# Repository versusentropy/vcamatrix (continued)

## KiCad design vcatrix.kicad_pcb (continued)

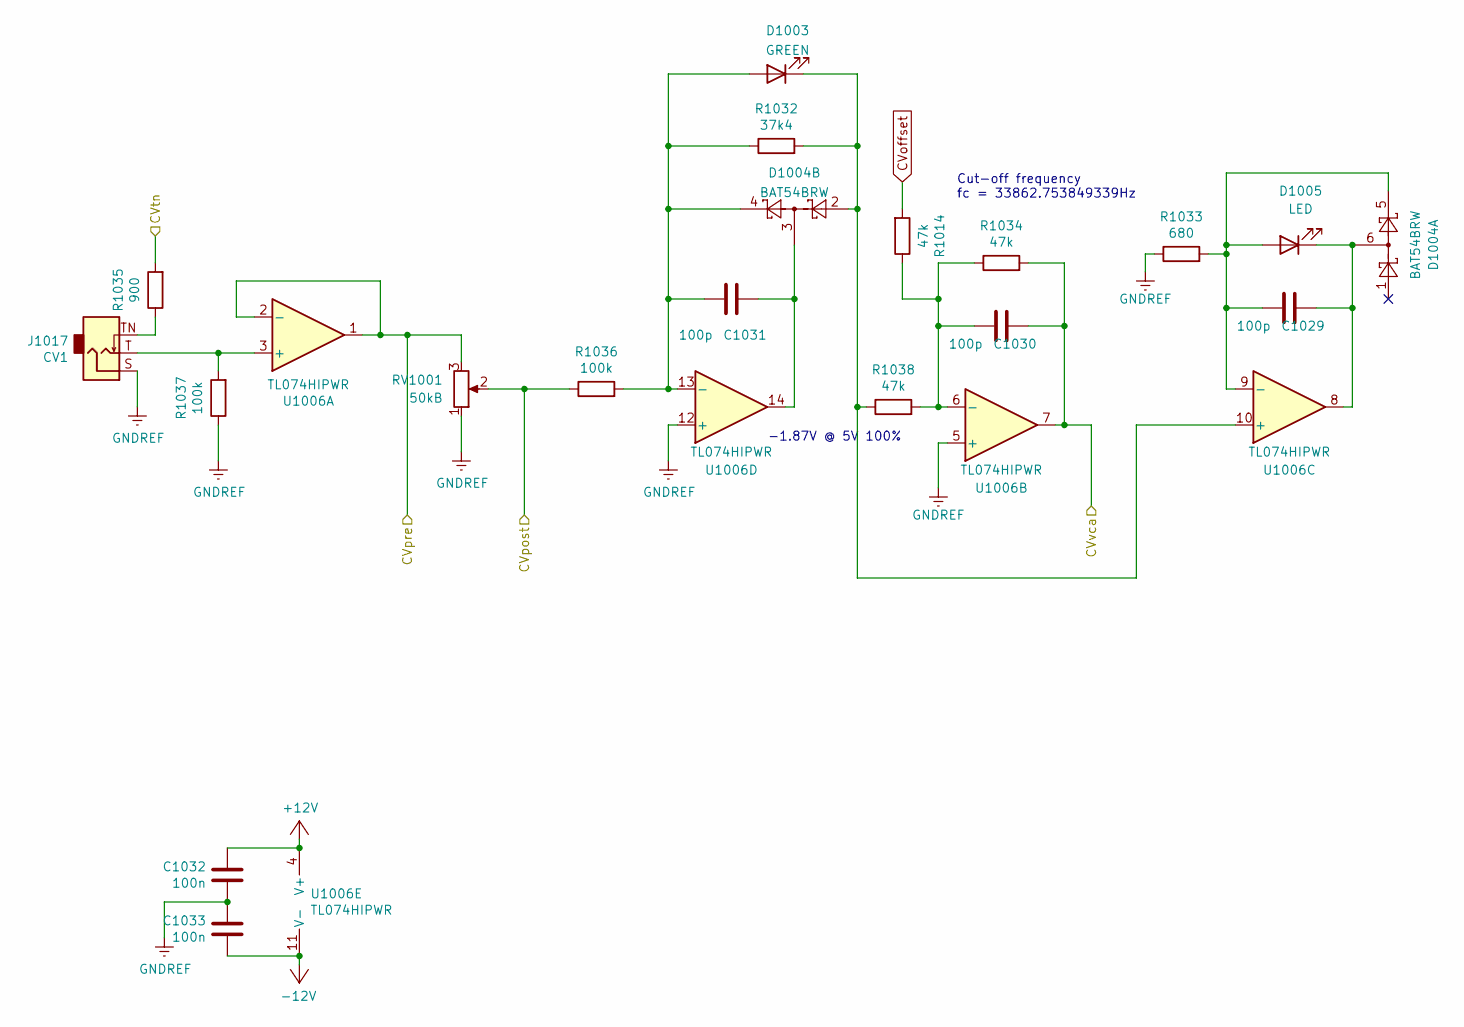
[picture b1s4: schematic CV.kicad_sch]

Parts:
C1029, C1030, C1031: 100p; C_0402_1005Metric; LCSC C1546
C1032, C1033: 100n; C_0402_1005Metric; LCSC C307331
D1003: GREEN; LED_0805_2012Metric; LCSC C98221
D1004: BAT54BRW; SOT-363_SC-70-6; LCSC C5240643
D1005: LED; LED_D3.0mm
J1017: CV1; Jack_3.5mm_QingPu_WQP-PJ398SM_Vertical_CircularHolesSMALL
R1014, R1034, R1038: 47k; R_0402_1005Metric; LCSC C358418
R1032: 37k4; R_0402_1005Metric; LCSC C103005
R1033: 680; R_0603_1608Metric; LCSC C23228
R1035: 900; R_0603_1608Metric; LCSC C3013565
R1036, R1037: 100k; R_0402_1005Metric; LCSC C317929
RV1001: 50kB; Potentiometer_Alpha_RD901F-40-00D_Single_Vertical
U1006: TL074HIPWR; TSSOP-14_4.4x5mm_P0.65mm; LCSC C4370424

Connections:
+12V: C1032.2, U1006.4 (V+); also elsewhere on the board
-12V: C1033.1, U1006.11 (V-); also elsewhere on the board
/5Vref: R1035.2; also elsewhere on the board
/VCA row1/CV-A/CVvca: C1030.1, R1034.2, U1006.7; also elsewhere on the board
/VCA row1/CVpostA: R1036.1, RV1001.2; also elsewhere on the board
/VCA row1/CVpreA: RV1001.3, U1006.1, U1006.2 (-); also elsewhere on the board
CVoffset: R1014.2; also elsewhere on the board
GNDREF: C1032.1, C1033.2, J1017.S, R1033.1, R1037.1, RV1001.1, U1006.5 (+), U1006.12 (+); also elsewhere on the board
unnamed: C1031.1, D1004.3, U1006.14
unnamed: C1031.2, D1003.2 (A), D1004.4, R1032.1, R1036.2, U1006.13 (-)
unnamed: D1003.1 (K), D1004.2, R1032.2, R1038.1, U1006.10 (+)
unnamed: C1029.2, D1004.5, D1005.2 (A), R1033.2, U1006.9 (-)
unnamed: C1029.1, D1004.6, D1005.1 (K), U1006.8
unnamed: J1017.TN, R1035.1
unnamed: J1017.T, R1037.2, U1006.3 (+)
unnamed: C1030.2, R1014.1, R1034.1, R1038.2, U1006.6 (-)

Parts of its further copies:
C1101, C1102, C1103, C1201, C1202, C1203, C1301, C1302, C1303, C2001, C2002, C2003, C2101, C2102, C2103, C2201, C2202, C2203, C2301, C2302, C2303, C3001, C3002, C3003, C3101, C3102, C3103, C3201, C3202, C3203, C3301, C3302, C3303, C4001, C4002, C4003, C4101, C4102, C4103, C4201, C4202, C4203, C4301, C4302, C4303: 100p; C_0402_1005Metric; LCSC C1546
C1104, C1105, C1204, C1205, C1304, C1305, C2004, C2005, C2104, C2105, C2204, C2205, C2304, C2305, C3004, C3005, C3104, C3105, C3204, C3205, C3304, C3305, C4004, C4005, C4104, C4105, C4204, C4205, C4304, C4305: 100n; C_0402_1005Metric; LCSC C307331
D1101, D1201, D1301, D2001, D2101, D2201, D2301, D3001, D3101, D3201, D3301, D4001, D4101, D4201, D4301: GREEN; LED_0805_2012Metric; LCSC C98221
D1102, D1202, D1302, D2002, D2102, D2202, D2302, D3002, D3102, D3202, D3302, D4002, D4102, D4202, D4302: BAT54BRW; SOT-363_SC-70-6; LCSC C5240643
D1103, D1203, D1303, D2003, D2103, D2203, D2303, D3003, D3103, D3203, D3303, D4003, D4103, D4203, D4303: LED; LED_D3.0mm
J1101, J1201, J1301, J2001, J2101, J2201, J2301, J3001, J3101, J3201, J3301, J4001, J4101, J4201, J4301: CV1; Jack_3.5mm_QingPu_WQP-PJ398SM_Vertical_CircularHolesSMALL
R1015, R1016, R1017, R1018, R1023, R1024, R1025, R1026, R1027, R1028, R1029, R1030, R1031, R1053, R1054, R1103, R1107, R1203, R1207, R1303, R1307, R2003, R2007, R2103, R2107, R2203, R2207, R2303, R2307, R3003, R3007, R3103, R3107, R3203, R3207, R3303, R3307, R4003, R4007, R4103, R4107, R4203, R4207, R4303, R4307: 47k; R_0402_1005Metric; LCSC C358418
R1101, R1201, R1301, R2001, R2101, R2201, R2301, R3001, R3101, R3201, R3301, R4001, R4101, R4201, R4301: 37k4; R_0402_1005Metric; LCSC C103005
R1102, R1202, R1302, R2002, R2102, R2202, R2302, R3002, R3102, R3202, R3302, R4002, R4102, R4202, R4302: 680; R_0603_1608Metric; LCSC C23228
R1104, R1204, R1304, R2004, R2104, R2204, R2304, R3004, R3104, R3204, R3304, R4004, R4104, R4204, R4304: 900; R_0603_1608Metric; LCSC C3013565
R1105, R1106, R1205, R1206, R1305, R1306, R2005, R2006, R2105, R2106, R2205, R2206, R2305, R2306, R3005, R3006, R3105, R3106, R3205, R3206, R3305, R3306, R4005, R4006, R4105, R4106, R4205, R4206, R4305, R4306: 100k; R_0402_1005Metric; LCSC C317929
RV1101, RV1201, RV1301, RV2001, RV2101, RV2201, RV2301, RV3001, RV3101, RV3201, RV3301, RV4001, RV4101, RV4201, RV4301: 50kB; Potentiometer_Alpha_RD901F-40-00D_Single_Vertical
U1101, U1201, U1301, U2001, U2101, U2201, U2301, U3001, U3101, U3201, U3301, U4001, U4101, U4201, U4301: TL074HIPWR; TSSOP-14_4.4x5mm_P0.65mm; LCSC C4370424

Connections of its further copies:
+12V: C1104.2, C1204.2, C1304.2, C2004.2, C2104.2, C2204.2, C2304.2, C3004.2, C3104.2, C3204.2, C3304.2, C4004.2, C4104.2, C4204.2, C4304.2, U1101.4 (V+), U1201.4 (V+), U1301.4 (V+), U2001.4 (V+), U2101.4 (V+), U2201.4 (V+), U2301.4 (V+), U3001.4 (V+), U3101.4 (V+), U3201.4 (V+), U3301.4 (V+), U4001.4 (V+), U4101.4 (V+), U4201.4 (V+), U4301.4 (V+); also elsewhere on the board
-12V: C1105.1, C1205.1, C1305.1, C2005.1, C2105.1, C2205.1, C2305.1, C3005.1, C3105.1, C3205.1, C3305.1, C4005.1, C4105.1, C4205.1, C4305.1, U1101.11 (V-), U1201.11 (V-), U1301.11 (V-), U2001.11 (V-), U2101.11 (V-), U2201.11 (V-), U2301.11 (V-), U3001.11 (V-), U3101.11 (V-), U3201.11 (V-), U3301.11 (V-), U4001.11 (V-), U4101.11 (V-), U4201.11 (V-), U4301.11 (V-); also elsewhere on the board
/5Vref: R1104.2, R1204.2, R1304.2; also elsewhere on the board
/VCA row1/CV-B/CVvca: C1102.1, R1103.2, U1101.7; also elsewhere on the board
/VCA row1/CV-C/CVvca: C1202.1, R1203.2, U1201.7; also elsewhere on the board
/VCA row1/CV-D/CVvca: C1302.1, R1303.2, U1301.7; also elsewhere on the board
/VCA row1/CVpostB: R1105.1, RV1101.2; also elsewhere on the board
/VCA row1/CVpostC: R1205.1, RV1201.2; also elsewhere on the board
/VCA row1/CVpostD: R1305.1, RV1301.2; also elsewhere on the board
/VCA row1/CVpreB: RV1101.3, U1101.1, U1101.2 (-); also elsewhere on the board
/VCA row1/CVpreC: RV1201.3, U1201.1, U1201.2 (-); also elsewhere on the board
/VCA row1/CVpreD: RV1301.3, U1301.1, U1301.2 (-); also elsewhere on the board
/VCA row2/CV-A/CVvca: C2002.1, R2003.2, U2001.7; also elsewhere on the board
/VCA row2/CV-B/CVvca: C2102.1, R2103.2, U2101.7; also elsewhere on the board
/VCA row2/CV-C/CVvca: C2202.1, R2203.2, U2201.7; also elsewhere on the board
/VCA row2/CV-D/CVvca: C2302.1, R2303.2, U2301.7; also elsewhere on the board
/VCA row2/CVpostA: R2005.1, RV2001.2
/VCA row2/CVpostB: R2105.1, RV2101.2
/VCA row2/CVpostC: R2205.1, RV2201.2
/VCA row2/CVpostD: R2305.1, RV2301.2
/VCA row2/CVpreA: R3004.2, RV2001.3, U2001.1, U2001.2 (-)
/VCA row2/CVpreB: R3104.2, RV2101.3, U2101.1, U2101.2 (-)
/VCA row2/CVpreC: R3204.2, RV2201.3, U2201.1, U2201.2 (-)
/VCA row2/CVpreD: R3304.2, RV2301.3, U2301.1, U2301.2 (-)
/VCA row2/CVtnA: R2004.2; also elsewhere on the board
/VCA row2/CVtnB: R2104.2; also elsewhere on the board
/VCA row2/CVtnC: R2204.2; also elsewhere on the board
/VCA row2/CVtnD: R2304.2; also elsewhere on the board
/VCA row3/CV-A/CVvca: C3002.1, R3003.2, U3001.7; also elsewhere on the board
/VCA row3/CV-B/CVvca: C3102.1, R3103.2, U3101.7; also elsewhere on the board
/VCA row3/CV-C/CVvca: C3202.1, R3203.2, U3201.7; also elsewhere on the board
/VCA row3/CV-D/CVvca: C3302.1, R3303.2, U3301.7; also elsewhere on the board
/VCA row3/CVpostA: R3005.1, RV3001.2; also elsewhere on the board
/VCA row3/CVpostB: R3105.1, RV3101.2; also elsewhere on the board
/VCA row3/CVpostC: R3205.1, RV3201.2; also elsewhere on the board
/VCA row3/CVpostD: R3305.1, RV3301.2; also elsewhere on the board
/VCA row3/CVpreA: RV3001.3, U3001.1, U3001.2 (-); also elsewhere on the board
/VCA row3/CVpreB: RV3101.3, U3101.1, U3101.2 (-); also elsewhere on the board
/VCA row3/CVpreC: RV3201.3, U3201.1, U3201.2 (-); also elsewhere on the board
/VCA row3/CVpreD: RV3301.3, U3301.1, U3301.2 (-); also elsewhere on the board
/VCA row4/CV-A/CVvca: C4002.1, R4003.2, U4001.7; also elsewhere on the board
/VCA row4/CV-B/CVvca: C4102.1, R4103.2, U4101.7; also elsewhere on the board
/VCA row4/CV-C/CVvca: C4202.1, R4203.2, U4201.7; also elsewhere on the board
/VCA row4/CV-D/CVvca: C4302.1, R4303.2, U4301.7; also elsewhere on the board
/VCA row4/CVpostA: R4005.1, RV4001.2
/VCA row4/CVpostB: R4105.1, RV4101.2
/VCA row4/CVpostC: R4205.1, RV4201.2
/VCA row4/CVpostD: R4305.1, RV4301.2
/VCA row4/CVpreA: RV4001.3, U4001.1, U4001.2 (-)
/VCA row4/CVpreB: RV4101.3, U4101.1, U4101.2 (-)
/VCA row4/CVpreC: RV4201.3, U4201.1, U4201.2 (-)
/VCA row4/CVpreD: RV4301.3, U4301.1, U4301.2 (-)
/VCA row4/CVtnA: R4004.2; also elsewhere on the board
/VCA row4/CVtnB: R4104.2; also elsewhere on the board
/VCA row4/CVtnC: R4204.2; also elsewhere on the board
/VCA row4/CVtnD: R4304.2; also elsewhere on the board
CVoffset: R1015.2, R1016.2, R1017.2, R1018.2, R1023.2, R1024.2, R1025.2, R1026.2, R1027.2, R1028.2, R1029.2, R1030.2, R1031.2, R1053.2, R1054.2; also elsewhere on the board
GNDREF: C1104.1, C1105.2, C1204.1, C1205.2, C1304.1, C1305.2, C2004.1, C2005.2, C2104.1, C2105.2, C2204.1, C2205.2, C2304.1, C2305.2, C3004.1, C3005.2, C3104.1, C3105.2, C3204.1, C3205.2, C3304.1, C3305.2, C4004.1, C4005.2, C4104.1, C4105.2, C4204.1, C4205.2, C4304.1, C4305.2, J1101.S, J1201.S, J1301.S, J2001.S, J2101.S, J2201.S, J2301.S, J3001.S, J3101.S, J3201.S, J3301.S, J4001.S, J4101.S, J4201.S, J4301.S, R1102.1, R1106.1, R1202.1, R1206.1, R1302.1, R1306.1, R2002.1, R2006.1, R2102.1, R2106.1, R2202.1, R2206.1, R2302.1, R2306.1, R3002.1, R3006.1, R3102.1, R3106.1, R3202.1, R3206.1, R3302.1, R3306.1, R4002.1, R4006.1, R4102.1, R4106.1, R4202.1, R4206.1, R4302.1, R4306.1, RV1101.1, RV1201.1, RV1301.1, RV2001.1, RV2101.1, RV2201.1, RV2301.1, RV3001.1, RV3101.1, RV3201.1, RV3301.1, RV4001.1, RV4101.1, RV4201.1, RV4301.1, U1101.5 (+), U1101.12 (+), U1201.5 (+), U1201.12 (+), U1301.5 (+), U1301.12 (+), U2001.5 (+), U2001.12 (+), U2101.5 (+), U2101.12 (+), U2201.5 (+), U2201.12 (+), U2301.5 (+), U2301.12 (+), U3001.5 (+), U3001.12 (+), U3101.5 (+), U3101.12 (+), U3201.5 (+), U3201.12 (+), U3301.5 (+), U3301.12 (+), U4001.5 (+), U4001.12 (+), U4101.5 (+), U4101.12 (+), U4201.5 (+), U4201.12 (+), U4301.5 (+), U4301.12 (+); also elsewhere on the board
unnamed: C1103.1, D1102.3, U1101.14
unnamed: C1203.1, D1202.3, U1201.14
unnamed: C1303.1, D1302.3, U1301.14
unnamed: C2003.1, D2002.3, U2001.14
unnamed: C2103.1, D2102.3, U2101.14
unnamed: C2203.1, D2202.3, U2201.14
unnamed: C2303.1, D2302.3, U2301.14
unnamed: C3003.1, D3002.3, U3001.14
unnamed: C3103.1, D3102.3, U3101.14
unnamed: C3203.1, D3202.3, U3201.14
unnamed: C3303.1, D3302.3, U3301.14
unnamed: C4003.1, D4002.3, U4001.14
unnamed: C4103.1, D4102.3, U4101.14
unnamed: C4203.1, D4202.3, U4201.14
unnamed: C4303.1, D4302.3, U4301.14
unnamed: C1103.2, D1101.2 (A), D1102.4, R1101.1, R1105.2, U1101.13 (-)
unnamed: D1101.1 (K), D1102.2, R1101.2, R1107.1, U1101.10 (+)
unnamed: C1101.2, D1102.5, D1103.2 (A), R1102.2, U1101.9 (-)
unnamed: C1101.1, D1102.6, D1103.1 (K), U1101.8
unnamed: C1203.2, D1201.2 (A), D1202.4, R1201.1, R1205.2, U1201.13 (-)
unnamed: D1201.1 (K), D1202.2, R1201.2, R1207.1, U1201.10 (+)
unnamed: C1201.2, D1202.5, D1203.2 (A), R1202.2, U1201.9 (-)
unnamed: C1201.1, D1202.6, D1203.1 (K), U1201.8
unnamed: C1303.2, D1301.2 (A), D1302.4, R1301.1, R1305.2, U1301.13 (-)
unnamed: D1301.1 (K), D1302.2, R1301.2, R1307.1, U1301.10 (+)
unnamed: C1301.2, D1302.5, D1303.2 (A), R1302.2, U1301.9 (-)
unnamed: C1301.1, D1302.6, D1303.1 (K), U1301.8
unnamed: C2003.2, D2001.2 (A), D2002.4, R2001.1, R2005.2, U2001.13 (-)
unnamed: D2001.1 (K), D2002.2, R2001.2, R2007.1, U2001.10 (+)
unnamed: C2001.2, D2002.5, D2003.2 (A), R2002.2, U2001.9 (-)
unnamed: C2001.1, D2002.6, D2003.1 (K), U2001.8
unnamed: C2103.2, D2101.2 (A), D2102.4, R2101.1, R2105.2, U2101.13 (-)
unnamed: D2101.1 (K), D2102.2, R2101.2, R2107.1, U2101.10 (+)
unnamed: C2101.2, D2102.5, D2103.2 (A), R2102.2, U2101.9 (-)
unnamed: C2101.1, D2102.6, D2103.1 (K), U2101.8
unnamed: C2203.2, D2201.2 (A), D2202.4, R2201.1, R2205.2, U2201.13 (-)
unnamed: D2201.1 (K), D2202.2, R2201.2, R2207.1, U2201.10 (+)
unnamed: C2201.2, D2202.5, D2203.2 (A), R2202.2, U2201.9 (-)
unnamed: C2201.1, D2202.6, D2203.1 (K), U2201.8
unnamed: C2303.2, D2301.2 (A), D2302.4, R2301.1, R2305.2, U2301.13 (-)
unnamed: D2301.1 (K), D2302.2, R2301.2, R2307.1, U2301.10 (+)
unnamed: C2301.2, D2302.5, D2303.2 (A), R2302.2, U2301.9 (-)
unnamed: C2301.1, D2302.6, D2303.1 (K), U2301.8
unnamed: C3003.2, D3001.2 (A), D3002.4, R3001.1, R3005.2, U3001.13 (-)
unnamed: D3001.1 (K), D3002.2, R3001.2, R3007.1, U3001.10 (+)
unnamed: C3001.2, D3002.5, D3003.2 (A), R3002.2, U3001.9 (-)
unnamed: C3001.1, D3002.6, D3003.1 (K), U3001.8
unnamed: C3103.2, D3101.2 (A), D3102.4, R3101.1, R3105.2, U3101.13 (-)
unnamed: D3101.1 (K), D3102.2, R3101.2, R3107.1, U3101.10 (+)
unnamed: C3101.2, D3102.5, D3103.2 (A), R3102.2, U3101.9 (-)
unnamed: C3101.1, D3102.6, D3103.1 (K), U3101.8
unnamed: C3203.2, D3201.2 (A), D3202.4, R3201.1, R3205.2, U3201.13 (-)
unnamed: D3201.1 (K), D3202.2, R3201.2, R3207.1, U3201.10 (+)
unnamed: C3201.2, D3202.5, D3203.2 (A), R3202.2, U3201.9 (-)
unnamed: C3201.1, D3202.6, D3203.1 (K), U3201.8
unnamed: C3303.2, D3301.2 (A), D3302.4, R3301.1, R3305.2, U3301.13 (-)
unnamed: D3301.1 (K), D3302.2, R3301.2, R3307.1, U3301.10 (+)
unnamed: C3301.2, D3302.5, D3303.2 (A), R3302.2, U3301.9 (-)
unnamed: C3301.1, D3302.6, D3303.1 (K), U3301.8
unnamed: C4003.2, D4001.2 (A), D4002.4, R4001.1, R4005.2, U4001.13 (-)
unnamed: D4001.1 (K), D4002.2, R4001.2, R4007.1, U4001.10 (+)
unnamed: C4001.2, D4002.5, D4003.2 (A), R4002.2, U4001.9 (-)
unnamed: C4001.1, D4002.6, D4003.1 (K), U4001.8
unnamed: C4103.2, D4101.2 (A), D4102.4, R4101.1, R4105.2, U4101.13 (-)
unnamed: D4101.1 (K), D4102.2, R4101.2, R4107.1, U4101.10 (+)
unnamed: C4101.2, D4102.5, D4103.2 (A), R4102.2, U4101.9 (-)
unnamed: C4101.1, D4102.6, D4103.1 (K), U4101.8
unnamed: C4203.2, D4201.2 (A), D4202.4, R4201.1, R4205.2, U4201.13 (-)
unnamed: D4201.1 (K), D4202.2, R4201.2, R4207.1, U4201.10 (+)
unnamed: C4201.2, D4202.5, D4203.2 (A), R4202.2, U4201.9 (-)
unnamed: C4201.1, D4202.6, D4203.1 (K), U4201.8
unnamed: C4303.2, D4301.2 (A), D4302.4, R4301.1, R4305.2, U4301.13 (-)
unnamed: D4301.1 (K), D4302.2, R4301.2, R4307.1, U4301.10 (+)
unnamed: C4301.2, D4302.5, D4303.2 (A), R4302.2, U4301.9 (-)
unnamed: C4301.1, D4302.6, D4303.1 (K), U4301.8
unnamed: J1101.TN, R1104.1
unnamed: J1201.TN, R1204.1
unnamed: J1301.TN, R1304.1
unnamed: J2001.TN, R2004.1
unnamed: J2101.TN, R2104.1
unnamed: J2201.TN, R2204.1
unnamed: J2301.TN, R2304.1
unnamed: J3001.TN, R3004.1
unnamed: J3101.TN, R3104.1
unnamed: J3201.TN, R3204.1
unnamed: J3301.TN, R3304.1
unnamed: J4001.TN, R4004.1
unnamed: J4101.TN, R4104.1
unnamed: J4201.TN, R4204.1
unnamed: J4301.TN, R4304.1
unnamed: J1101.T, R1106.2, U1101.3 (+)
unnamed: C1102.2, R1015.1, R1103.1, R1107.2, U1101.6 (-)
unnamed: J1201.T, R1206.2, U1201.3 (+)
unnamed: C1202.2, R1016.1, R1203.1, R1207.2, U1201.6 (-)
unnamed: J1301.T, R1306.2, U1301.3 (+)
unnamed: C1302.2, R1017.1, R1303.1, R1307.2, U1301.6 (-)
unnamed: J2001.T, R2006.2, U2001.3 (+)
unnamed: C2002.2, R1018.1, R2003.1, R2007.2, U2001.6 (-)
unnamed: J2101.T, R2106.2, U2101.3 (+)
unnamed: C2102.2, R1023.1, R2103.1, R2107.2, U2101.6 (-)
unnamed: J2201.T, R2206.2, U2201.3 (+)
unnamed: C2202.2, R1024.1, R2203.1, R2207.2, U2201.6 (-)
unnamed: J2301.T, R2306.2, U2301.3 (+)
unnamed: C2302.2, R1025.1, R2303.1, R2307.2, U2301.6 (-)
unnamed: J3001.T, R3006.2, U3001.3 (+)
unnamed: C3002.2, R1026.1, R3003.1, R3007.2, U3001.6 (-)
unnamed: J3101.T, R3106.2, U3101.3 (+)
unnamed: C3102.2, R1027.1, R3103.1, R3107.2, U3101.6 (-)
unnamed: J3201.T, R3206.2, U3201.3 (+)
unnamed: C3202.2, R1028.1, R3203.1, R3207.2, U3201.6 (-)
unnamed: J3301.T, R3306.2, U3301.3 (+)
unnamed: C3302.2, R1029.1, R3303.1, R3307.2, U3301.6 (-)
unnamed: J4001.T, R4006.2, U4001.3 (+)
unnamed: C4002.2, R1030.1, R4003.1, R4007.2, U4001.6 (-)
unnamed: J4101.T, R4106.2, U4101.3 (+)
unnamed: C4102.2, R1031.1, R4103.1, R4107.2, U4101.6 (-)
unnamed: J4201.T, R4206.2, U4201.3 (+)
unnamed: C4202.2, R1053.1, R4203.1, R4207.2, U4201.6 (-)
unnamed: J4301.T, R4306.2, U4301.3 (+)
unnamed: C4302.2, R1054.1, R4303.1, R4307.2, U4301.6 (-)

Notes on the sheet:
Cut-off frequency fc = 33862.753849339Hz
-1.87V @ 5V 100%

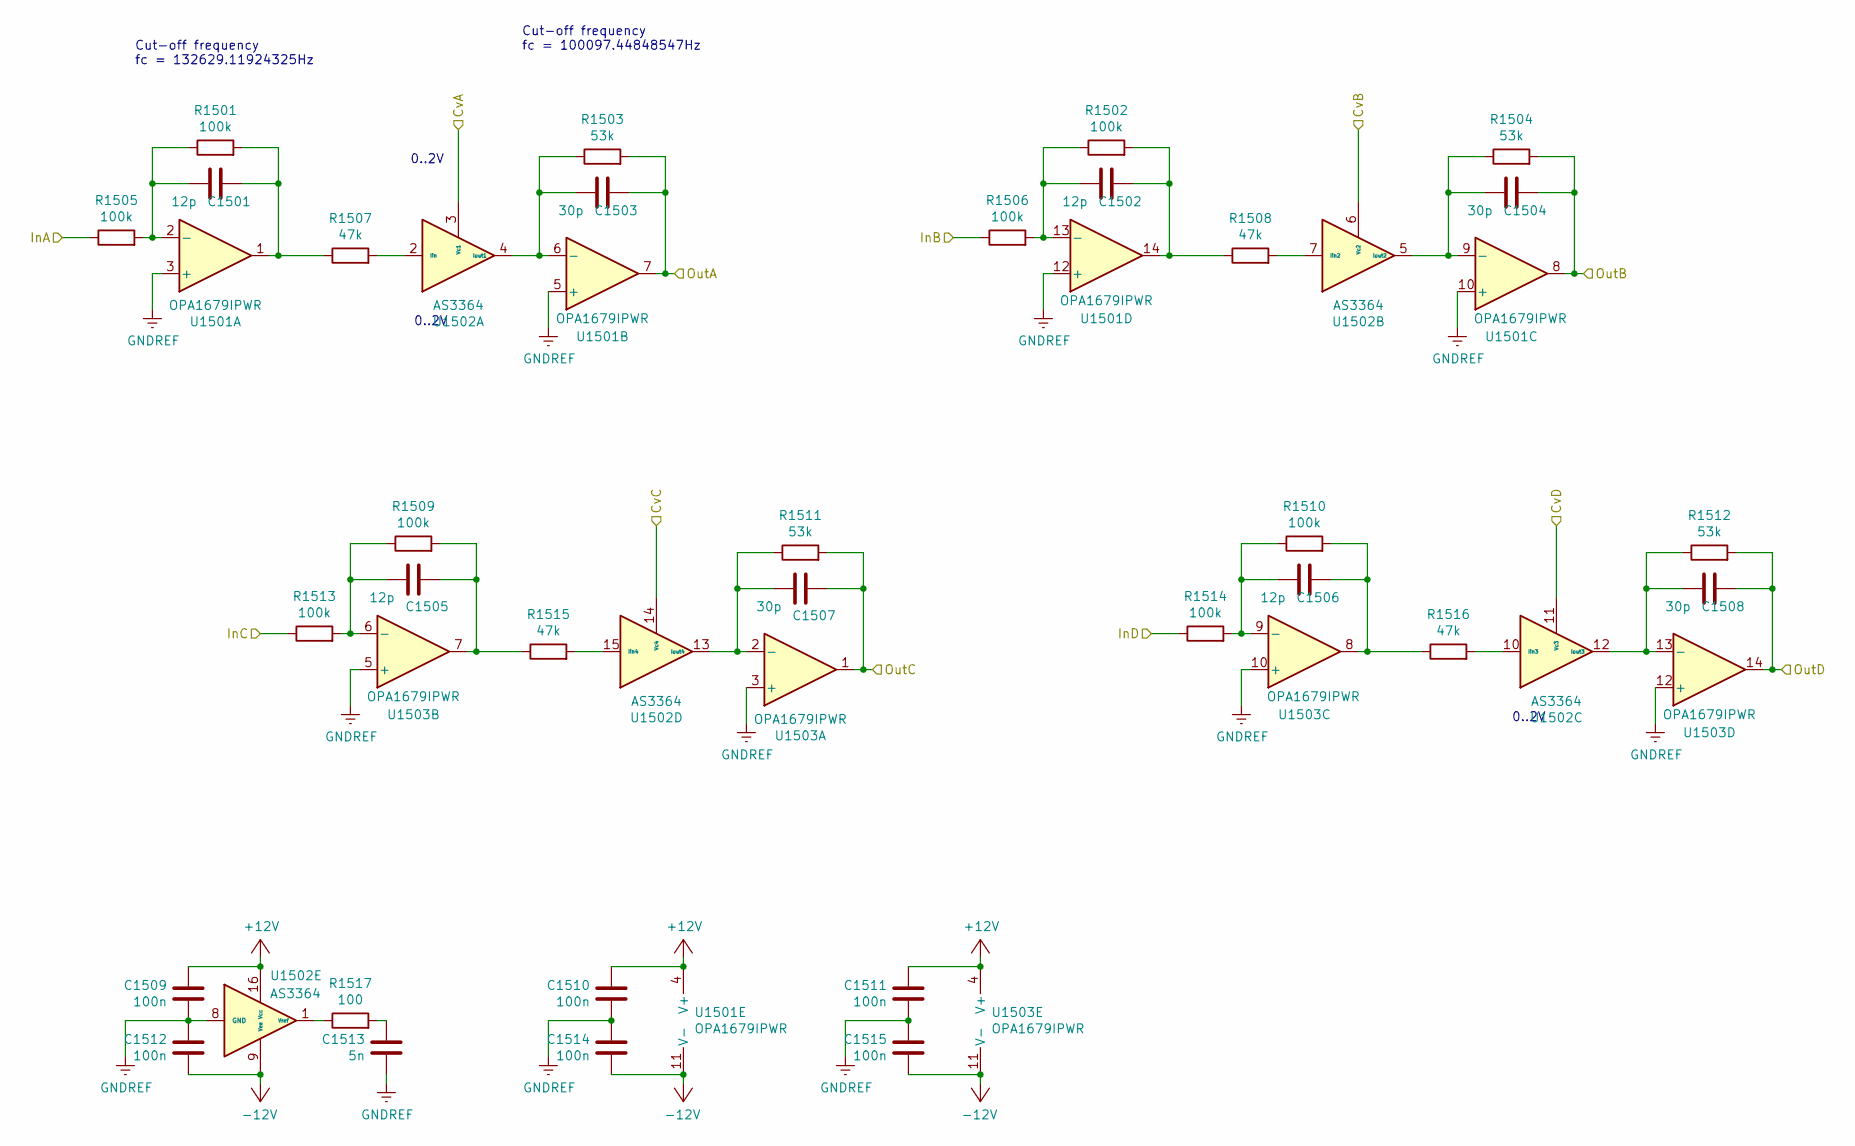
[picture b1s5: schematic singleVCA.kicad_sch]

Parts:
C1501, C1502, C1505, C1506: 12p; C_0402_1005Metric; LCSC C1547
C1503, C1504, C1507, C1508: 30p; C_0402_1005Metric; LCSC C1570
C1509, C1510, C1511, C1512, C1514, C1515: 100n; C_0402_1005Metric; LCSC C307331
C1513: 5n; C_0603_1608Metric; LCSC C1625
R1501, R1502, R1505, R1506, R1509, R1510, R1513, R1514: 100k; R_0402_1005Metric; LCSC C317929
R1503, R1504, R1511, R1512: 53k; R_0402_1005Metric; LCSC C852836
R1507, R1508, R1515, R1516: 47k; R_0402_1005Metric; LCSC C358418
R1517: 100; R_0402_1005Metric; LCSC C25076
U1501, U1503: OPA1679IPWR; TSSOP-14_4.4x5mm_P0.65mm; LCSC C2057264
U1502: AS3364; SOIC-16_3.9x9.9mm_P1.27mm; LCSC C9900006840

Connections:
+12V: C1509.2, C1510.2, C1511.2, U1501.4 (V+), U1502.16 (Vcc), U1503.4 (V+); also elsewhere on the board
-12V: C1512.1, C1514.1, C1515.1, U1501.11 (V-), U1502.9 (Vee), U1503.11 (V-); also elsewhere on the board
/MIX-A1/OutA: C1503.1, R1503.2, U1501.7; also elsewhere on the board
/MIX-A1/OutB: C1504.1, R1504.2, U1501.8; also elsewhere on the board
/MIX-B1/OutA: C1507.1, R1511.2, U1503.1; also elsewhere on the board
/MIX-B1/OutB: C1508.1, R1512.2, U1503.14; also elsewhere on the board
/VCA row1/CV-A/CVvca: U1502.3 (Vc1); also elsewhere on the board
/VCA row1/CV-B/CVvca: U1502.6 (Vc2); also elsewhere on the board
/VCA row1/CV-C/CVvca: U1502.14 (Vc4); also elsewhere on the board
/VCA row1/CV-D/CVvca: U1502.11 (Vc3); also elsewhere on the board
/VCA row1/InA: R1505.1; also elsewhere on the board
/VCA row1/InB: R1506.1; also elsewhere on the board
/VCA row1/InC: R1513.1; also elsewhere on the board
/VCA row1/InD: R1514.1; also elsewhere on the board
GNDREF: C1509.1, C1510.1, C1511.1, C1512.2, C1513.1, C1514.2, C1515.2, U1501.3 (+), U1501.5 (+), U1501.10 (+), U1501.12 (+), U1502.8 (GND), U1503.3 (+), U1503.5 (+), U1503.10 (+), U1503.12 (+); also elsewhere on the board
unnamed: C1501.1, R1501.2, R1507.1, U1501.1
unnamed: C1502.1, R1502.2, R1508.1, U1501.14
unnamed: C1505.1, R1509.2, R1515.1, U1503.7
unnamed: C1506.1, R1510.2, R1516.1, U1503.8
unnamed: C1513.2, R1517.2
unnamed: C1501.2, R1501.1, R1505.2, U1501.2 (-)
unnamed: C1503.2, R1503.1, U1501.6 (-), U1502.4 (Iout1)
unnamed: C1504.2, R1504.1, U1501.9 (-), U1502.5 (Iout2)
unnamed: C1502.2, R1502.1, R1506.2, U1501.13 (-)
unnamed: R1507.2, U1502.2 (Iin)
unnamed: R1508.2, U1502.7 (Iin2)
unnamed: R1516.2, U1502.10 (Iin3)
unnamed: C1508.2, R1512.1, U1502.12 (Iout3), U1503.13 (-)
unnamed: R1515.2, U1502.15 (Iin4)
unnamed: C1507.2, R1511.1, U1502.13 (Iout4), U1503.2 (-)
unnamed: R1517.1, U1502.1 (Vref)
unnamed: C1505.2, R1509.1, R1513.2, U1503.6 (-)
unnamed: C1506.2, R1510.1, R1514.2, U1503.9 (-)

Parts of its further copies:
C2501, C2502, C2505, C2506, C3501, C3502, C3505, C3506, C4501, C4502, C4505, C4506: 12p; C_0402_1005Metric; LCSC C1547
C2503, C2504, C2507, C2508, C3503, C3504, C3507, C3508, C4503, C4504, C4507, C4508: 30p; C_0402_1005Metric; LCSC C1570
C2509, C2510, C2511, C2512, C2514, C2515, C3509, C3510, C3511, C3512, C3514, C3515, C4509, C4510, C4511, C4512, C4514, C4515: 100n; C_0402_1005Metric; LCSC C307331
C2513, C3513, C4513: 5n; C_0603_1608Metric; LCSC C1625
R2501, R2502, R2505, R2506, R2509, R2510, R2513, R2514, R3501, R3502, R3505, R3506, R3509, R3510, R3513, R3514, R4501, R4502, R4505, R4506, R4509, R4510, R4513, R4514: 100k; R_0402_1005Metric; LCSC C317929
R2503, R2504, R2511, R2512, R3503, R3504, R3511, R3512, R4503, R4504, R4511, R4512: 53k; R_0402_1005Metric; LCSC C852836
R2507, R2508, R2515, R2516, R3507, R3508, R3515, R3516, R4507, R4508, R4515, R4516: 47k; R_0402_1005Metric; LCSC C358418
R2517, R3517, R4517: 100; R_0402_1005Metric; LCSC C25076
U2501, U2503, U3501, U3503, U4501, U4503: OPA1679IPWR; TSSOP-14_4.4x5mm_P0.65mm; LCSC C2057264
U2502, U3502, U4502: AS3364; SOIC-16_3.9x9.9mm_P1.27mm; LCSC C9900006840

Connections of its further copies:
+12V: C2509.2, C2510.2, C2511.2, C3509.2, C3510.2, C3511.2, C4509.2, C4510.2, C4511.2, U2501.4 (V+), U2502.16 (Vcc), U2503.4 (V+), U3501.4 (V+), U3502.16 (Vcc), U3503.4 (V+), U4501.4 (V+), U4502.16 (Vcc), U4503.4 (V+); also elsewhere on the board
-12V: C2512.1, C2514.1, C2515.1, C3512.1, C3514.1, C3515.1, C4512.1, C4514.1, C4515.1, U2501.11 (V-), U2502.9 (Vee), U2503.11 (V-), U3501.11 (V-), U3502.9 (Vee), U3503.11 (V-), U4501.11 (V-), U4502.9 (Vee), U4503.11 (V-); also elsewhere on the board
/MIX-A2/OutA: C2503.1, R2503.2, U2501.7; also elsewhere on the board
/MIX-A2/OutB: C2504.1, R2504.2, U2501.8; also elsewhere on the board
/MIX-A3/OutA: C3503.1, R3503.2, U3501.7; also elsewhere on the board
/MIX-A3/OutB: C3504.1, R3504.2, U3501.8; also elsewhere on the board
/MIX-A4/OutA: C4503.1, R4503.2, U4501.7; also elsewhere on the board
/MIX-A4/OutB: C4504.1, R4504.2, U4501.8; also elsewhere on the board
/MIX-B2/OutA: C2507.1, R2511.2, U2503.1; also elsewhere on the board
/MIX-B2/OutB: C2508.1, R2512.2, U2503.14; also elsewhere on the board
/MIX-B3/OutA: C3507.1, R3511.2, U3503.1; also elsewhere on the board
/MIX-B3/OutB: C3508.1, R3512.2, U3503.14; also elsewhere on the board
/MIX-B4/OutA: C4507.1, R4511.2, U4503.1; also elsewhere on the board
/MIX-B4/OutB: C4508.1, R4512.2, U4503.14; also elsewhere on the board
/VCA row2/CV-A/CVvca: U2502.3 (Vc1); also elsewhere on the board
/VCA row2/CV-B/CVvca: U2502.6 (Vc2); also elsewhere on the board
/VCA row2/CV-C/CVvca: U2502.14 (Vc4); also elsewhere on the board
/VCA row2/CV-D/CVvca: U2502.11 (Vc3); also elsewhere on the board
/VCA row2/InA: R2505.1; also elsewhere on the board
/VCA row2/InB: R2506.1; also elsewhere on the board
/VCA row2/InC: R2513.1; also elsewhere on the board
/VCA row2/InD: R2514.1; also elsewhere on the board
/VCA row3/CV-A/CVvca: U3502.3 (Vc1); also elsewhere on the board
/VCA row3/CV-B/CVvca: U3502.6 (Vc2); also elsewhere on the board
/VCA row3/CV-C/CVvca: U3502.14 (Vc4); also elsewhere on the board
/VCA row3/CV-D/CVvca: U3502.11 (Vc3); also elsewhere on the board
/VCA row3/InA: R3505.1; also elsewhere on the board
/VCA row3/InB: R3506.1; also elsewhere on the board
/VCA row3/InC: R3513.1; also elsewhere on the board
/VCA row3/InD: R3514.1; also elsewhere on the board
/VCA row4/CV-A/CVvca: U4502.3 (Vc1); also elsewhere on the board
/VCA row4/CV-B/CVvca: U4502.6 (Vc2); also elsewhere on the board
/VCA row4/CV-C/CVvca: U4502.14 (Vc4); also elsewhere on the board
/VCA row4/CV-D/CVvca: U4502.11 (Vc3); also elsewhere on the board
/VCA row4/InA: R4505.1; also elsewhere on the board
/VCA row4/InB: R4506.1; also elsewhere on the board
/VCA row4/InC: R4513.1; also elsewhere on the board
/VCA row4/InD: R4514.1; also elsewhere on the board
GNDREF: C2509.1, C2510.1, C2511.1, C2512.2, C2513.1, C2514.2, C2515.2, C3509.1, C3510.1, C3511.1, C3512.2, C3513.1, C3514.2, C3515.2, C4509.1, C4510.1, C4511.1, C4512.2, C4513.1, C4514.2, C4515.2, U2501.3 (+), U2501.5 (+), U2501.10 (+), U2501.12 (+), U2502.8 (GND), U2503.3 (+), U2503.5 (+), U2503.10 (+), U2503.12 (+), U3501.3 (+), U3501.5 (+), U3501.10 (+), U3501.12 (+), U3502.8 (GND), U3503.3 (+), U3503.5 (+), U3503.10 (+), U3503.12 (+), U4501.3 (+), U4501.5 (+), U4501.10 (+), U4501.12 (+), U4502.8 (GND), U4503.3 (+), U4503.5 (+), U4503.10 (+), U4503.12 (+); also elsewhere on the board
unnamed: C2501.1, R2501.2, R2507.1, U2501.1
unnamed: C2502.1, R2502.2, R2508.1, U2501.14
unnamed: C2505.1, R2509.2, R2515.1, U2503.7
unnamed: C2506.1, R2510.2, R2516.1, U2503.8
unnamed: C2513.2, R2517.2
unnamed: C3501.1, R3501.2, R3507.1, U3501.1
unnamed: C3502.1, R3502.2, R3508.1, U3501.14
unnamed: C3505.1, R3509.2, R3515.1, U3503.7
unnamed: C3506.1, R3510.2, R3516.1, U3503.8
unnamed: C3513.2, R3517.2
unnamed: C4501.1, R4501.2, R4507.1, U4501.1
unnamed: C4502.1, R4502.2, R4508.1, U4501.14
unnamed: C4505.1, R4509.2, R4515.1, U4503.7
unnamed: C4506.1, R4510.2, R4516.1, U4503.8
unnamed: C4513.2, R4517.2
unnamed: C2501.2, R2501.1, R2505.2, U2501.2 (-)
unnamed: C2503.2, R2503.1, U2501.6 (-), U2502.4 (Iout1)
unnamed: C2504.2, R2504.1, U2501.9 (-), U2502.5 (Iout2)
unnamed: C2502.2, R2502.1, R2506.2, U2501.13 (-)
unnamed: R2507.2, U2502.2 (Iin)
unnamed: R2508.2, U2502.7 (Iin2)
unnamed: R2516.2, U2502.10 (Iin3)
unnamed: C2508.2, R2512.1, U2502.12 (Iout3), U2503.13 (-)
unnamed: R2515.2, U2502.15 (Iin4)
unnamed: C2507.2, R2511.1, U2502.13 (Iout4), U2503.2 (-)
unnamed: R2517.1, U2502.1 (Vref)
unnamed: C2505.2, R2509.1, R2513.2, U2503.6 (-)
unnamed: C2506.2, R2510.1, R2514.2, U2503.9 (-)
unnamed: C3501.2, R3501.1, R3505.2, U3501.2 (-)
unnamed: C3503.2, R3503.1, U3501.6 (-), U3502.4 (Iout1)
unnamed: C3504.2, R3504.1, U3501.9 (-), U3502.5 (Iout2)
unnamed: C3502.2, R3502.1, R3506.2, U3501.13 (-)
unnamed: R3507.2, U3502.2 (Iin)
unnamed: R3508.2, U3502.7 (Iin2)
unnamed: R3516.2, U3502.10 (Iin3)
unnamed: C3508.2, R3512.1, U3502.12 (Iout3), U3503.13 (-)
unnamed: R3515.2, U3502.15 (Iin4)
unnamed: C3507.2, R3511.1, U3502.13 (Iout4), U3503.2 (-)
unnamed: R3517.1, U3502.1 (Vref)
unnamed: C3505.2, R3509.1, R3513.2, U3503.6 (-)
unnamed: C3506.2, R3510.1, R3514.2, U3503.9 (-)
unnamed: C4501.2, R4501.1, R4505.2, U4501.2 (-)
unnamed: C4503.2, R4503.1, U4501.6 (-), U4502.4 (Iout1)
unnamed: C4504.2, R4504.1, U4501.9 (-), U4502.5 (Iout2)
unnamed: C4502.2, R4502.1, R4506.2, U4501.13 (-)
unnamed: R4507.2, U4502.2 (Iin)
unnamed: R4508.2, U4502.7 (Iin2)
unnamed: R4516.2, U4502.10 (Iin3)
unnamed: C4508.2, R4512.1, U4502.12 (Iout3), U4503.13 (-)
unnamed: R4515.2, U4502.15 (Iin4)
unnamed: C4507.2, R4511.1, U4502.13 (Iout4), U4503.2 (-)
unnamed: R4517.1, U4502.1 (Vref)
unnamed: C4505.2, R4509.1, R4513.2, U4503.6 (-)
unnamed: C4506.2, R4510.1, R4514.2, U4503.9 (-)

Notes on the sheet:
0..2V
Cut-off frequency fc = 132629.11924325Hz
Cut-off frequency fc = 100097.44848547Hz

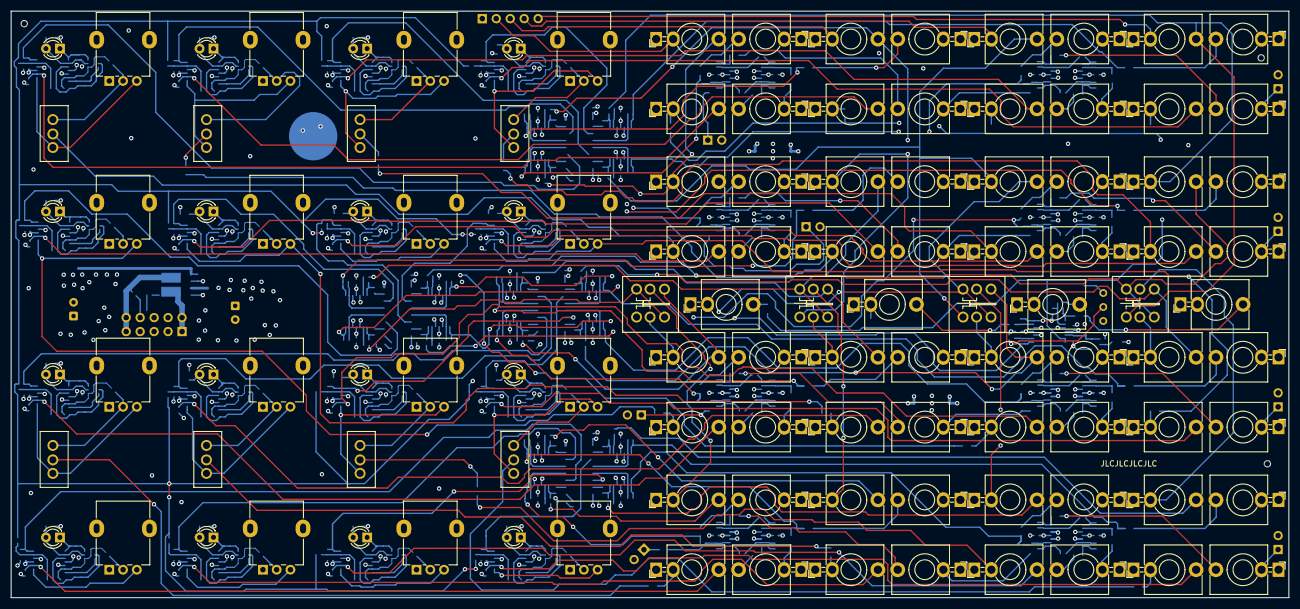
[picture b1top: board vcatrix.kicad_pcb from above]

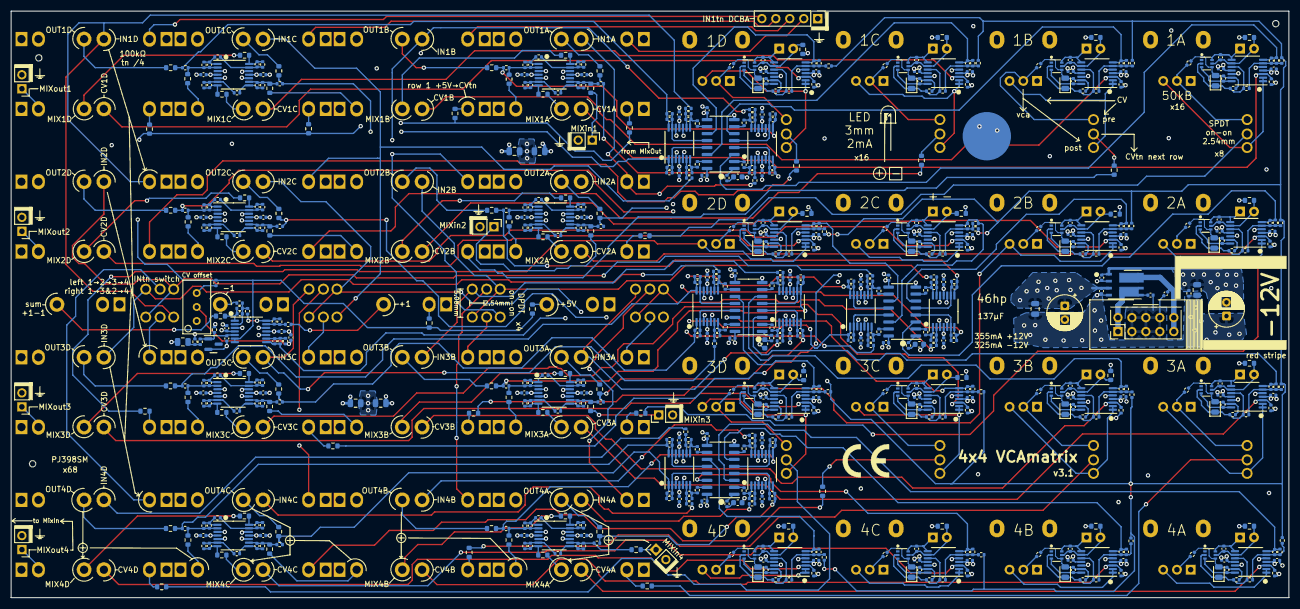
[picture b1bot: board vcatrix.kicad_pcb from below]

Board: 6 copper layers, 232.4 x 106.7 mm, 728 parts (613 on the bottom side), 437 nets.

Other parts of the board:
REF1, REF2, REF3: tooling-hole
